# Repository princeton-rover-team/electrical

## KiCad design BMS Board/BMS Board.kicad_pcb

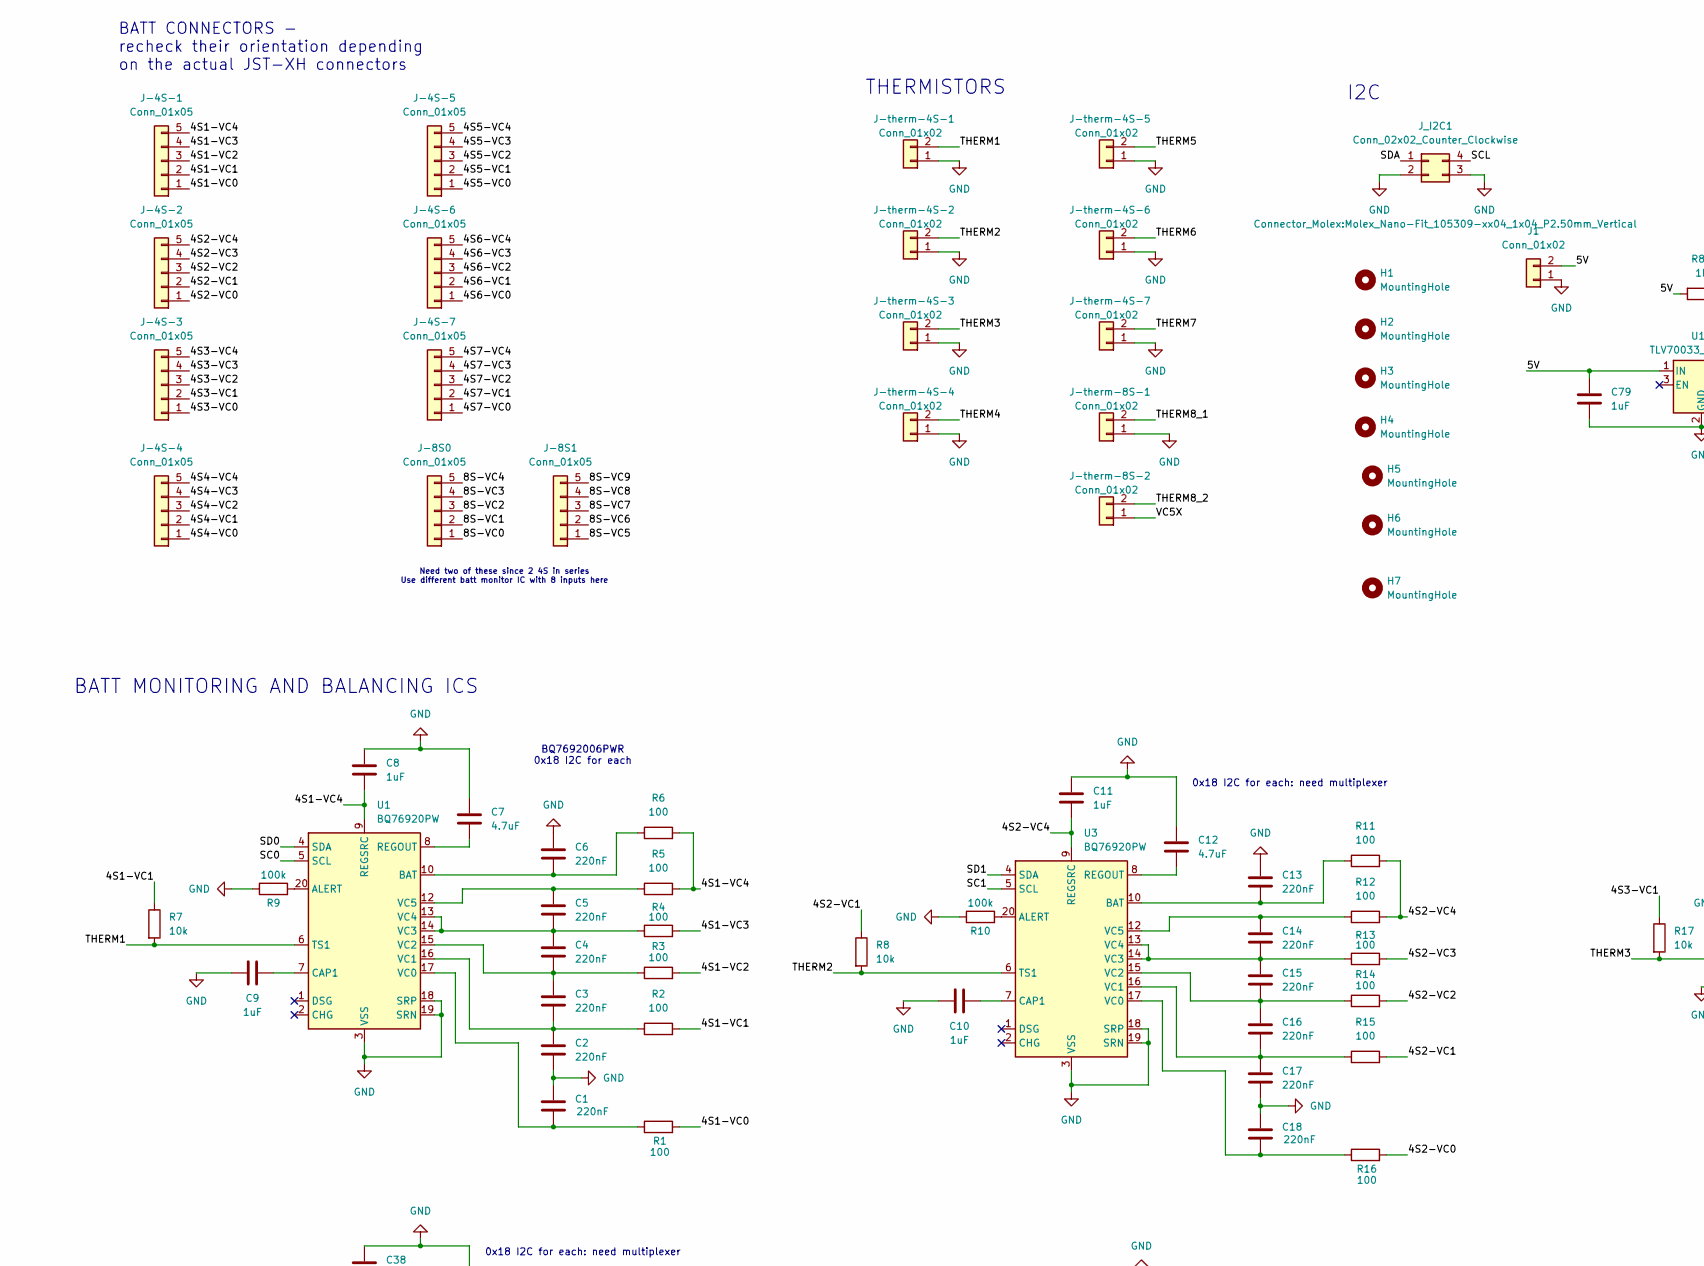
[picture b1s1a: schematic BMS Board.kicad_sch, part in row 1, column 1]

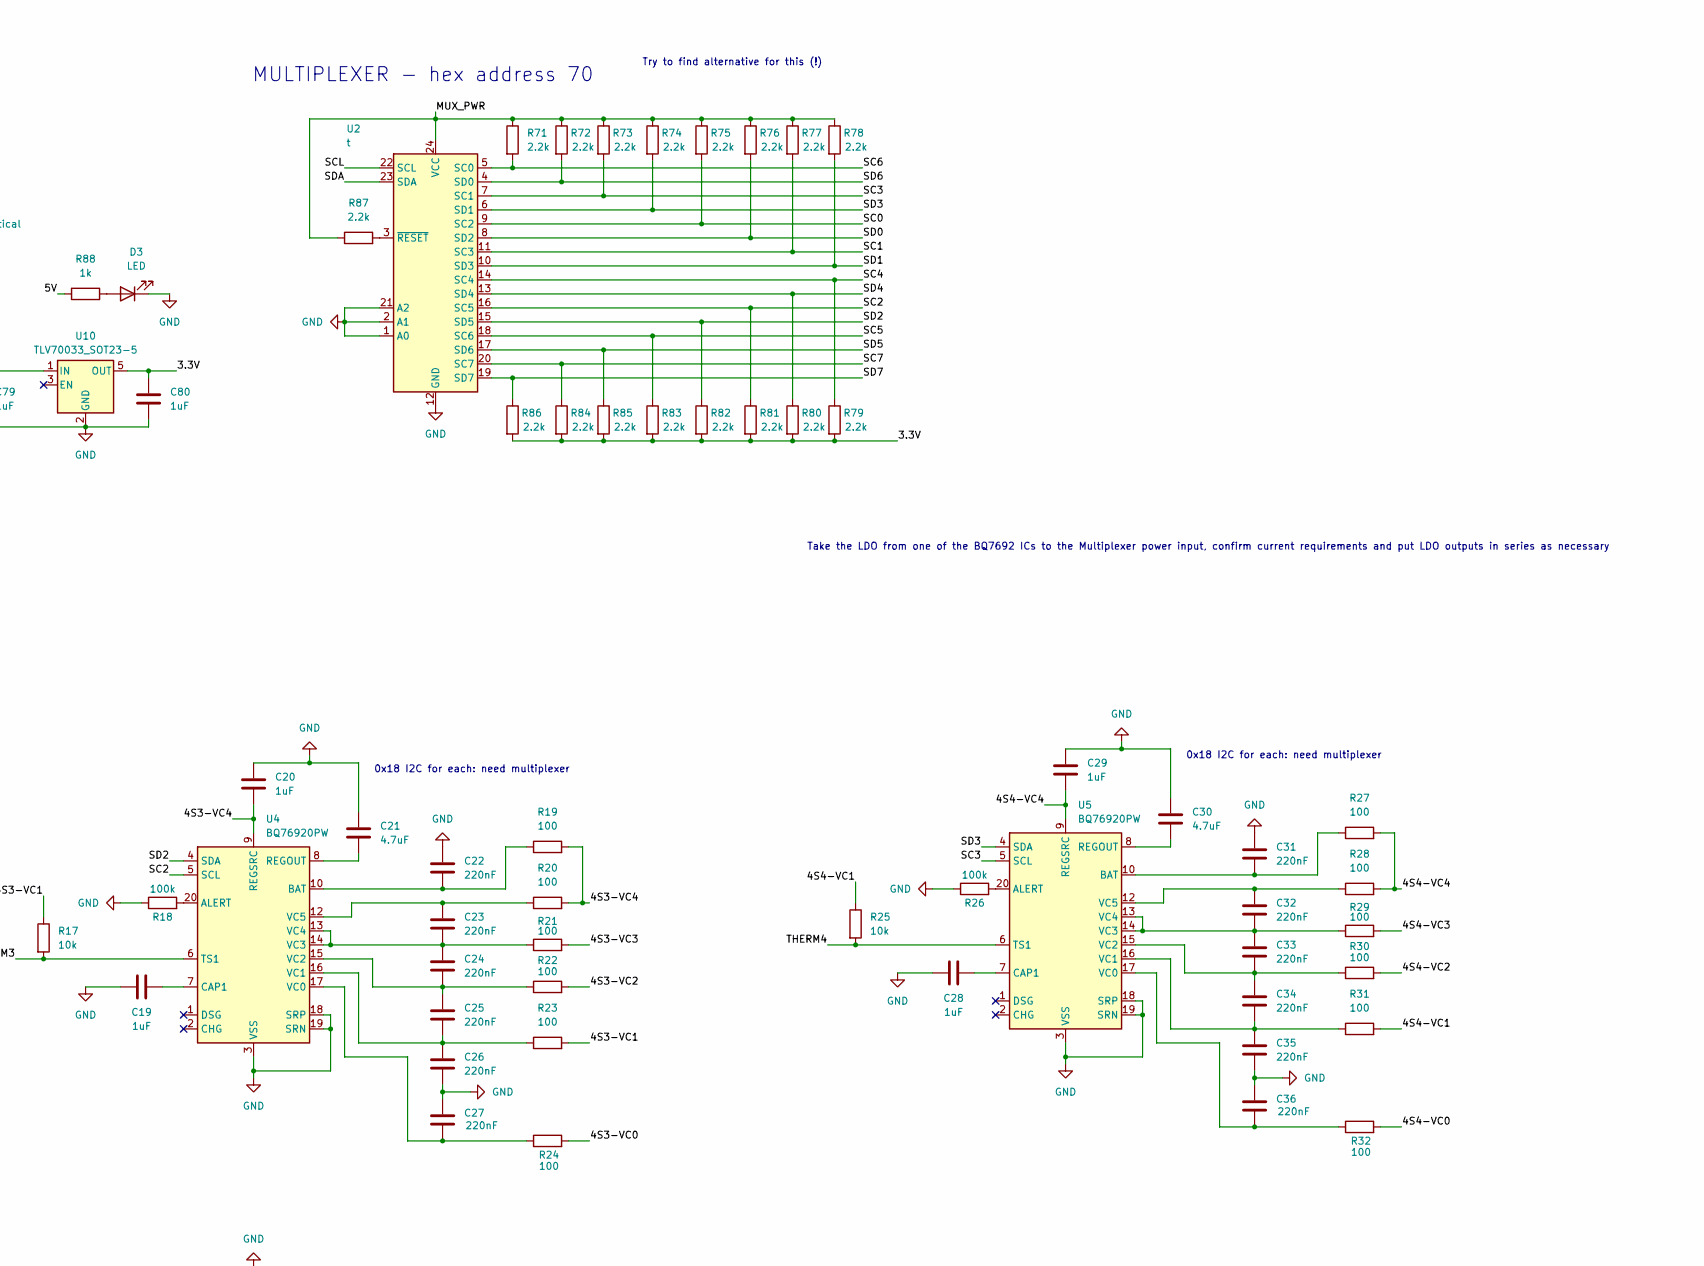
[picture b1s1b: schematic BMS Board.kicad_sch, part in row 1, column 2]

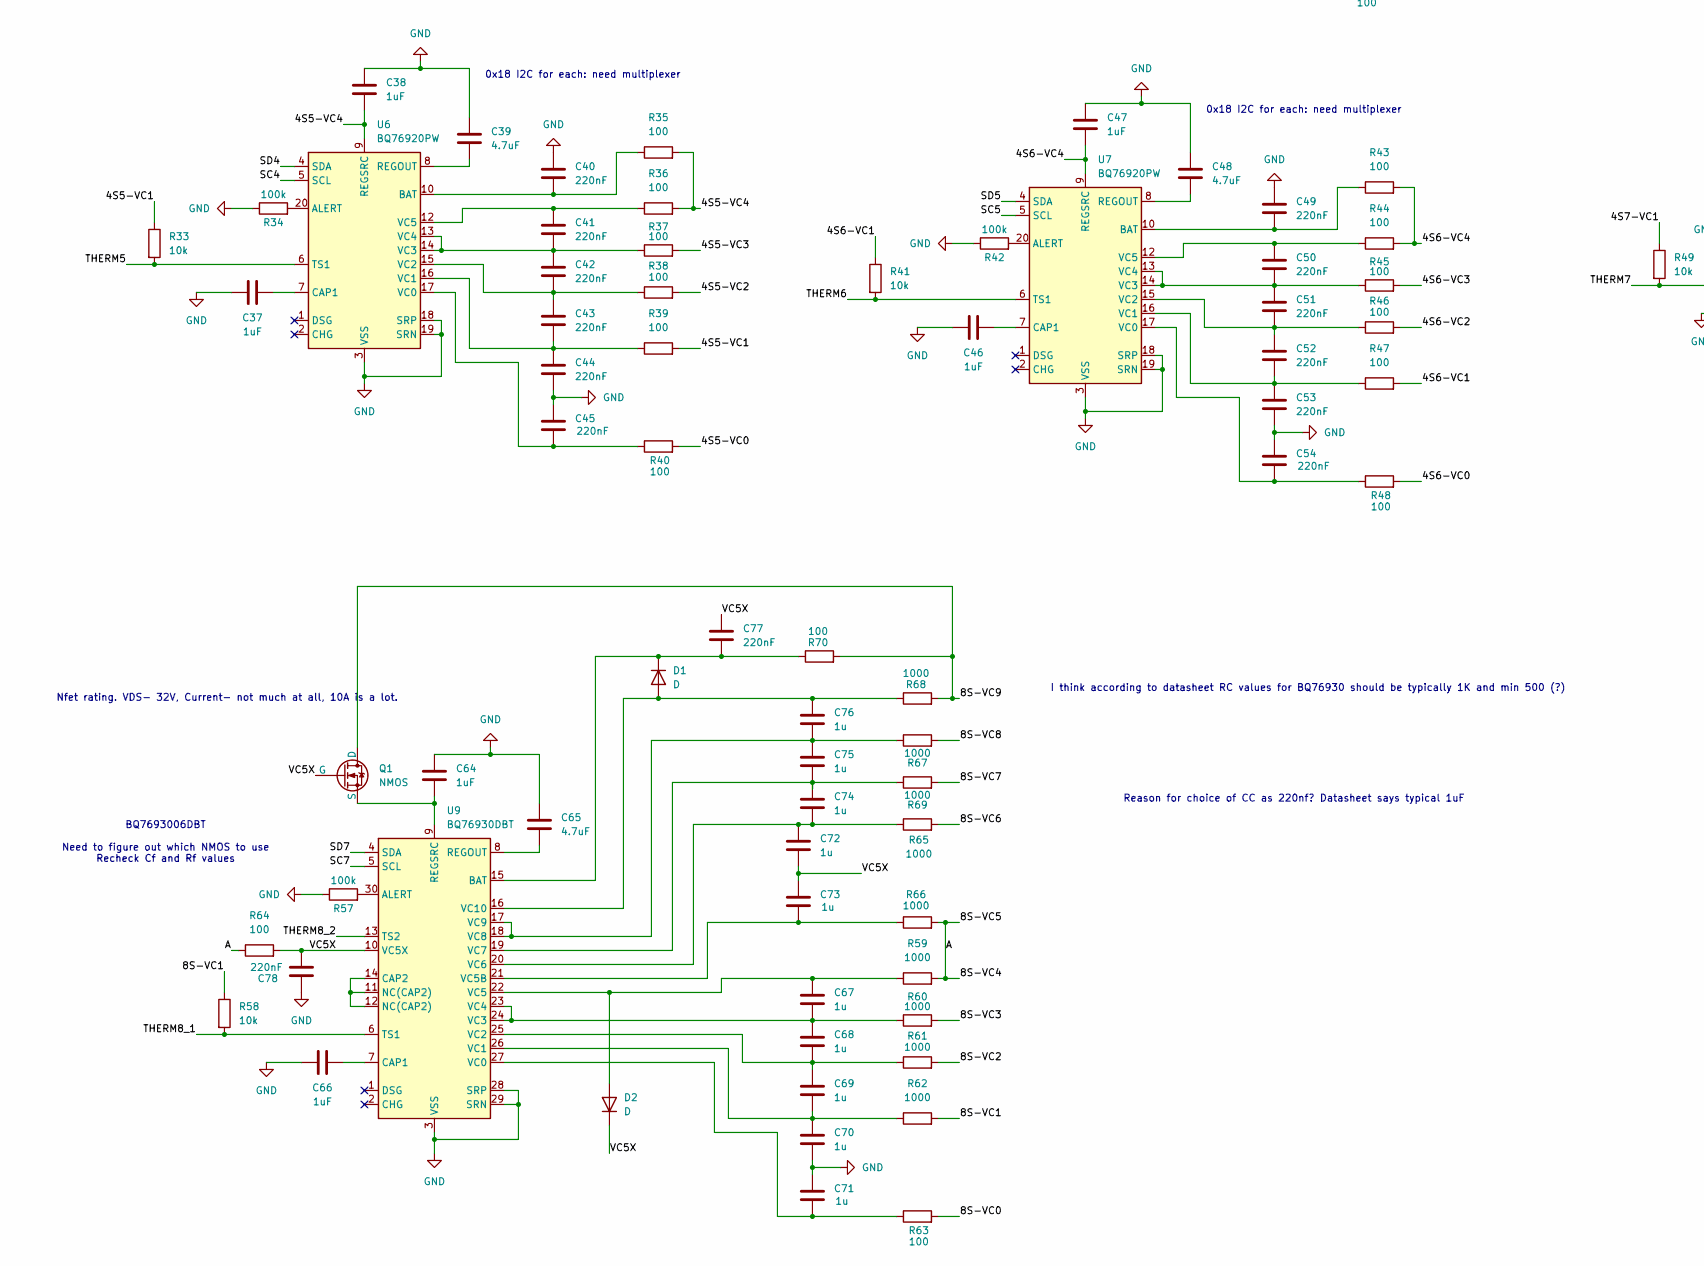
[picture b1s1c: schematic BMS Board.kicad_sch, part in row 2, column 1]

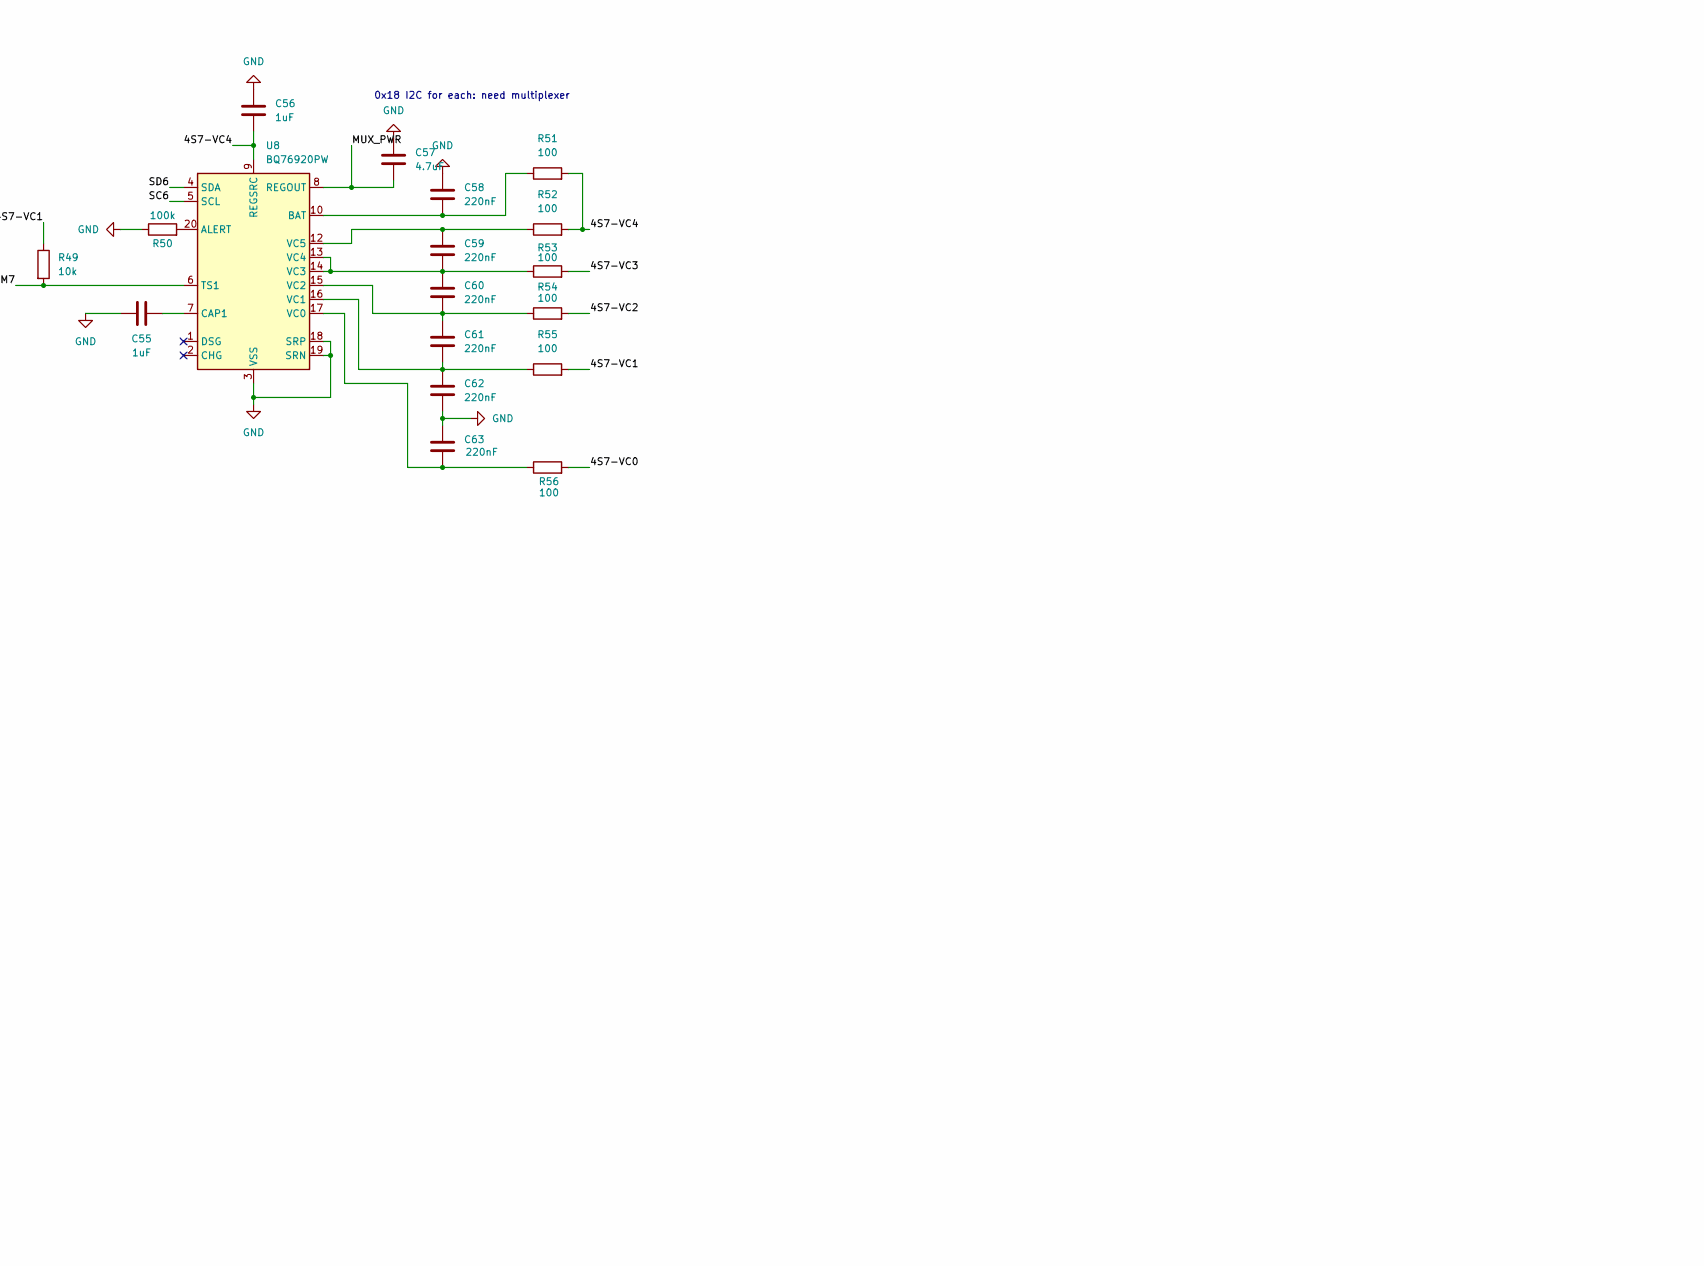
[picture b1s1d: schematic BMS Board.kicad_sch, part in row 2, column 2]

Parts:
C1, C2, C3, C4, C5, C6, C13, C14, C15, C16, C17, C18, C22, C23, C24, C25, C26, C27, C31, C32, C33, C34, C35, C36, C40, C41, C42, C43, C44, C45, C49, C50, C51, C52, C53, C54, C58, C59, C60, C61, C62, C63, C77, C78: 220nF; C_0603_1608Metric
C7, C12, C21, C30, C39, C48, C57, C65: 4.7uF; C_0603_1608Metric
C8, C9, C10, C11, C19, C20, C28, C29, C37, C38, C46, C47, C55, C56, C64, C66, C79, C80: 1uF; C_0603_1608Metric
C67, C68, C69, C70, C71, C72, C73, C74, C75, C76: 1u; C_0603_1608Metric
D1, D2: D; D_SOD-123
D3: LED; D_0603_1608Metric
H1, H2, H3, H4, H5, H6, H7: MountingHole; MountingHole_3.2mm_M3_DIN965
J1: Conn_01x02; AMASS_XT30UPB-F_1x02_P5.0mm_Vertical
J-4S-1, J-4S-2, J-4S-3, J-4S-4, J-4S-5, J-4S-6, J-4S-7, J-8S0, J-8S1: Conn_01x05; JST_XH_B5B-XH-A_1x05_P2.50mm_Vertical
J-therm-4S-1, J-therm-4S-2, J-therm-4S-3, J-therm-4S-4, J-therm-4S-5, J-therm-4S-6, J-therm-4S-7, J-therm-8S-1, J-therm-8S-2: Conn_01x02; Molex_KK-254_AE-6410-02A_1x02_P2.54mm_Vertical; MANUFACTURER_PART_NUMBER 768290102
J_I2C1: Conn_02x02_Counter_Clockwise; Molex_Nano-Fit_105309-xx04_1x04_P2.50mm_Vertical
Q1: NMOS; SOT-23
R1, R2, R3, R4, R5, R6, R11, R12, R13, R14, R15, R16, R19, R20, R21, R22, R23, R24, R27, R28, R29, R30, R31, R32, R35, R36, R37, R38, R39, R40, R43, R44, R45, R46, R47, R48, R51, R52, R53, R54, R55, R56, R63, R64, R70: 100; C_0603_1608Metric
R7, R8, R17, R25, R33, R41, R49, R58: 10k; C_0603_1608Metric
R9, R10, R18, R26, R34, R42, R50, R57: 100k; C_0603_1608Metric
R59, R60, R61, R62, R65, R66, R67, R68, R69: 1000; C_0603_1608Metric
R71, R72, R73, R74, R75, R76, R77, R78, R79, R80, R81, R82, R83, R84, R85, R86, R87: 2.2k; C_0603_1608Metric
R88: 1k; R_0805_2012Metric
U1, U3, U4, U5, U6, U7, U8: BQ76920PW; TSSOP-20_4.4x6.5mm_P0.65mm
U2: t; TSSOP-24_4.4x7.8mm_P0.65mm
U9: BQ76930DBT; TSSOP-30_4.4x7.8mm_P0.5mm
U10: TLV70033_SOT23-5; SOT-23-5

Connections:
/3.3V: C80.1, R79.2, R80.2, R81.2, R82.2, R83.2, R84.2, R85.2, R86.2, U10.5 (OUT)
/4S1-VC0: J-4S-1.1, R1.2
/4S1-VC1: J-4S-1.2, R2.2, R7.1
/4S1-VC2: J-4S-1.3, R3.2
/4S1-VC3: J-4S-1.4, R4.2
/4S1-VC4: C8.2, J-4S-1.5, R5.2, R6.2, U1.9 (REGSRC)
/4S2-VC0: J-4S-2.1, R16.2
/4S2-VC1: J-4S-2.2, R8.1, R15.2
/4S2-VC2: J-4S-2.3, R14.2
/4S2-VC3: J-4S-2.4, R13.2
/4S2-VC4: C11.2, J-4S-2.5, R11.2, R12.2, U3.9 (REGSRC)
/4S3-VC0: J-4S-3.1, R24.2
/4S3-VC1: J-4S-3.2, R17.1, R23.2
/4S3-VC2: J-4S-3.3, R22.2
/4S3-VC3: J-4S-3.4, R21.2
/4S3-VC4: C20.2, J-4S-3.5, R19.2, R20.2, U4.9 (REGSRC)
/4S4-VC0: J-4S-4.1, R32.2
/4S4-VC1: J-4S-4.2, R25.1, R31.2
/4S4-VC2: J-4S-4.3, R30.2
/4S4-VC3: J-4S-4.4, R29.2
/4S4-VC4: C29.2, J-4S-4.5, R27.2, R28.2, U5.9 (REGSRC)
/4S5-VC0: J-4S-5.1, R40.2
/4S5-VC1: J-4S-5.2, R33.1, R39.2
/4S5-VC2: J-4S-5.3, R38.2
/4S5-VC3: J-4S-5.4, R37.2
/4S5-VC4: C38.2, J-4S-5.5, R35.2, R36.2, U6.9 (REGSRC)
/4S6-VC0: J-4S-6.1, R48.2
/4S6-VC1: J-4S-6.2, R41.1, R47.2
/4S6-VC2: J-4S-6.3, R46.2
/4S6-VC3: J-4S-6.4, R45.2
/4S6-VC4: C47.2, J-4S-6.5, R43.2, R44.2, U7.9 (REGSRC)
/4S7-VC0: J-4S-7.1, R56.2
/4S7-VC1: J-4S-7.2, R49.1, R55.2
/4S7-VC2: J-4S-7.3, R54.2
/4S7-VC3: J-4S-7.4, R53.2
/4S7-VC4: C56.2, J-4S-7.5, R51.2, R52.2, U8.9 (REGSRC)
/5V: C79.1, J1.2, R88.2, U10.1 (IN)
/8S-VC0: J-8S0.1, R63.2
/8S-VC1: J-8S0.2, R58.1, R62.2
/8S-VC2: J-8S0.3, R61.2
/8S-VC3: J-8S0.4, R60.2
/8S-VC4: J-8S0.5, J-8S1.1, R59.2, R64.1, R66.2
/8S-VC6: J-8S1.2, R65.2
/8S-VC7: J-8S1.3, R69.2
/8S-VC8: J-8S1.4, R67.2
/8S-VC9: J-8S1.5, Q1.1 (D), R68.2, R70.2
/MUX_PWR: C57.2, R71.1, R72.1, R73.1, R74.1, R75.1, R76.1, R77.1, R78.1, R87.1, U2.24 (VCC), U8.8 (REGOUT)
/SC0: R75.2, U1.5 (SCL), U2.9 (SC2)
/SC1: R77.2, U2.11 (SC3), U3.5 (SCL)
/SC2: R81.1, U2.16 (SC5), U4.5 (SCL)
/SC3: R73.2, U2.7 (SC1), U5.5 (SCL)
/SC4: R79.1, U2.14 (SC4), U6.5 (SCL)
/SC5: R83.1, U2.18 (SC6), U7.5 (SCL)
/SC6: R71.2, U2.5 (SC0), U8.5 (SCL)
/SC7: R84.1, U2.20 (SC7), U9.5 (SCL)
/SCL: J_I2C1.4, U2.22 (SCL)
/SD0: R76.2, U1.4 (SDA), U2.8 (SD2)
/SD1: R78.2, U2.10 (SD3), U3.4 (SDA)
/SD2: R82.1, U2.15 (SD5), U4.4 (SDA)
/SD3: R74.2, U2.6 (SD1), U5.4 (SDA)
/SD4: R80.1, U2.13 (SD4), U6.4 (SDA)
/SD5: R85.1, U2.17 (SD6), U7.4 (SDA)
/SD6: R72.2, U2.4 (SD0), U8.4 (SDA)
/SD7: R86.1, U2.19 (SD7), U9.4 (SDA)
/SDA: J_I2C1.1, U2.23 (SDA)
/THERM1: J-therm-4S-1.2, R7.2, U1.6 (TS1)
/THERM2: J-therm-4S-2.2, R8.2, U3.6 (TS1)
/THERM3: J-therm-4S-3.2, R17.2, U4.6 (TS1)
/THERM4: J-therm-4S-4.2, R25.2, U5.6 (TS1)
/THERM5: J-therm-4S-5.2, R33.2, U6.6 (TS1)
/THERM6: J-therm-4S-6.2, R41.2, U7.6 (TS1)
/THERM7: J-therm-4S-7.2, R49.2, U8.6 (TS1)
/THERM8_1: J-therm-8S-1.2, R58.2, U9.6 (TS1)
/THERM8_2: J-therm-8S-2.2, U9.13 (TS2)
/VC5X: C72.2, C73.1, C77.1, C78.2, D2.1 (K), J-therm-8S-2.1, Q1.2 (G), R64.2, U9.10 (VC5X)
GND: C1.1, C2.2, C6.1, C7.1, C8.1, C9.2, C10.2, C11.1, C12.1, C13.1, C17.2, C18.1, C19.2, C20.1, C21.1, C22.1, C26.2, C27.1, C28.2, C29.1, C30.1, C31.1, C35.2, C36.1, C37.2, C38.1, C39.1, C40.1, C44.2, C45.1, C46.2, C47.1, C48.1, C49.1, C53.2, C54.1, C55.2, C56.1, C57.1, C58.1, C62.2, C63.1, C64.1, C65.1, C66.2, C70.2, C71.1, C78.1, C79.2, C80.2, D3.1 (K), J1.1, J-therm-4S-1.1, J-therm-4S-2.1, J-therm-4S-3.1, J-therm-4S-4.1, J-therm-4S-5.1, J-therm-4S-6.1, J-therm-4S-7.1, J-therm-8S-1.1, J_I2C1.2, J_I2C1.3, R9.1, R10.1, R18.1, R26.1, R34.1, R42.1, R50.1, R57.1, U1.3 (VSS), U1.18 (SRP), U1.19 (SRN), U2.1 (A0), U2.2 (A1), U2.12 (GND), U2.21 (A2), U3.3 (VSS), U3.18 (SRP), U3.19 (SRN), U4.3 (VSS), U4.18 (SRP), U4.19 (SRN), U5.3 (VSS), U5.18 (SRP), U5.19 (SRN), U6.3 (VSS), U6.18 (SRP), U6.19 (SRN), U7.3 (VSS), U7.18 (SRP), U7.19 (SRN), U8.3 (VSS), U8.18 (SRP), U8.19 (SRN), U9.3 (VSS), U9.28 (SRP), U9.29 (SRN), U10.2 (GND)
unnamed: C76.1, D1.2 (A), R68.1, U9.16 (VC10)
unnamed: C77.2, D1.1 (K), R70.1, U9.15 (BAT)
unnamed: C67.1, D2.2 (A), R59.1, U9.22 (VC5)
unnamed: D3.2 (A), R88.1
unnamed: C64.2, Q1.3 (S), U9.9 (REGSRC)
unnamed: R9.2, U1.20 (ALERT)
unnamed: C6.2, R6.1, U1.10 (BAT)
unnamed: C9.1, U1.7 (CAP1)
unnamed: C7.2, U1.8 (REGOUT)
unnamed: C1.2, R1.1, U1.17 (VC0)
unnamed: C2.1, C3.2, R2.1, U1.16 (VC1)
unnamed: C3.1, C4.2, R3.1, U1.15 (VC2)
unnamed: C4.1, C5.2, R4.1, U1.13 (VC4), U1.14 (VC3)
unnamed: C5.1, R5.1, U1.12 (VC5)
unnamed: R87.2, U2.3 (~RESET)
unnamed: R10.2, U3.20 (ALERT)
unnamed: C13.2, R11.1, U3.10 (BAT)
unnamed: C10.1, U3.7 (CAP1)
unnamed: C12.2, U3.8 (REGOUT)
unnamed: C18.2, R16.1, U3.17 (VC0)
unnamed: C16.2, C17.1, R15.1, U3.16 (VC1)
unnamed: C15.2, C16.1, R14.1, U3.15 (VC2)
unnamed: C14.2, C15.1, R13.1, U3.13 (VC4), U3.14 (VC3)
unnamed: C14.1, R12.1, U3.12 (VC5)
unnamed: R18.2, U4.20 (ALERT)
unnamed: C22.2, R19.1, U4.10 (BAT)
unnamed: C19.1, U4.7 (CAP1)
unnamed: C21.2, U4.8 (REGOUT)
unnamed: C27.2, R24.1, U4.17 (VC0)
unnamed: C25.2, C26.1, R23.1, U4.16 (VC1)
unnamed: C24.2, C25.1, R22.1, U4.15 (VC2)
unnamed: C23.2, C24.1, R21.1, U4.13 (VC4), U4.14 (VC3)
unnamed: C23.1, R20.1, U4.12 (VC5)
unnamed: R26.2, U5.20 (ALERT)
unnamed: C31.2, R27.1, U5.10 (BAT)
unnamed: C28.1, U5.7 (CAP1)
unnamed: C30.2, U5.8 (REGOUT)
unnamed: C36.2, R32.1, U5.17 (VC0)
unnamed: C34.2, C35.1, R31.1, U5.16 (VC1)
unnamed: C33.2, C34.1, R30.1, U5.15 (VC2)
unnamed: C32.2, C33.1, R29.1, U5.13 (VC4), U5.14 (VC3)
unnamed: C32.1, R28.1, U5.12 (VC5)
unnamed: R34.2, U6.20 (ALERT)
unnamed: C40.2, R35.1, U6.10 (BAT)
unnamed: C37.1, U6.7 (CAP1)
unnamed: C39.2, U6.8 (REGOUT)
unnamed: C45.2, R40.1, U6.17 (VC0)
unnamed: C43.2, C44.1, R39.1, U6.16 (VC1)
unnamed: C42.2, C43.1, R38.1, U6.15 (VC2)
unnamed: C41.2, C42.1, R37.1, U6.13 (VC4), U6.14 (VC3)
unnamed: C41.1, R36.1, U6.12 (VC5)
unnamed: R42.2, U7.20 (ALERT)
unnamed: C49.2, R43.1, U7.10 (BAT)
unnamed: C46.1, U7.7 (CAP1)
unnamed: C48.2, U7.8 (REGOUT)
unnamed: C54.2, R48.1, U7.17 (VC0)
unnamed: C52.2, C53.1, R47.1, U7.16 (VC1)
unnamed: C51.2, C52.1, R46.1, U7.15 (VC2)
unnamed: C50.2, C51.1, R45.1, U7.13 (VC4), U7.14 (VC3)
unnamed: C50.1, R44.1, U7.12 (VC5)
unnamed: R50.2, U8.20 (ALERT)
unnamed: C58.2, R51.1, U8.10 (BAT)
unnamed: C55.1, U8.7 (CAP1)
unnamed: C63.2, R56.1, U8.17 (VC0)
unnamed: C61.2, C62.1, R55.1, U8.16 (VC1)
unnamed: C60.2, C61.1, R54.1, U8.15 (VC2)
unnamed: C59.2, C60.1, R53.1, U8.13 (VC4), U8.14 (VC3)
unnamed: C59.1, R52.1, U8.12 (VC5)
unnamed: R57.2, U9.30 (ALERT)
unnamed: C66.1, U9.7 (CAP1)
unnamed: U9.11 (NC(CAP2)), U9.12 (NC(CAP2)), U9.14 (CAP2)
unnamed: C65.2, U9.8 (REGOUT)
unnamed: C71.2, R63.1, U9.27 (VC0)
unnamed: C69.2, C70.1, R62.1, U9.26 (VC1)
unnamed: C68.2, C69.1, R61.1, U9.25 (VC2)
unnamed: C67.2, C68.1, R60.1, U9.23 (VC4), U9.24 (VC3)
unnamed: C73.2, R66.1, U9.21 (VC5B)
unnamed: C72.1, C74.2, R65.1, U9.20 (VC6)
unnamed: C74.1, C75.2, R69.1, U9.19 (VC7)
unnamed: C75.1, C76.2, R67.1, U9.17 (VC9), U9.18 (VC8)

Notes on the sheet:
Reason for choice of CC as 220nf? Datasheet says typical 1uF
0x18 I2C for each: need multiplexer
Need two of these since 2 4S in series Use different batt monitor IC with 8 inputs here
I2C
BATT MONITORING AND BALANCING ICS
Take the LDO from one of the BQ7692 ICs to the Multiplexer power input, confirm current requirements and put LDO outputs in series as necessary
THERMISTORS
BATT CONNECTORS - recheck their orientation depending on the actual JST-XH connectors
I think according to datasheet RC values for BQ76930 should be typically 1K and min 500 (?)
BQ7692006PWR 0x18 I2C for each
MULTIPLEXER - hex address 70
Try to find alternative for this (!)
Nfet rating. VDS- 32V, Current- not much at all, 10A is a lot.
BQ7693006DBT Need to figure out which NMOS to use Recheck Cf and Rf values

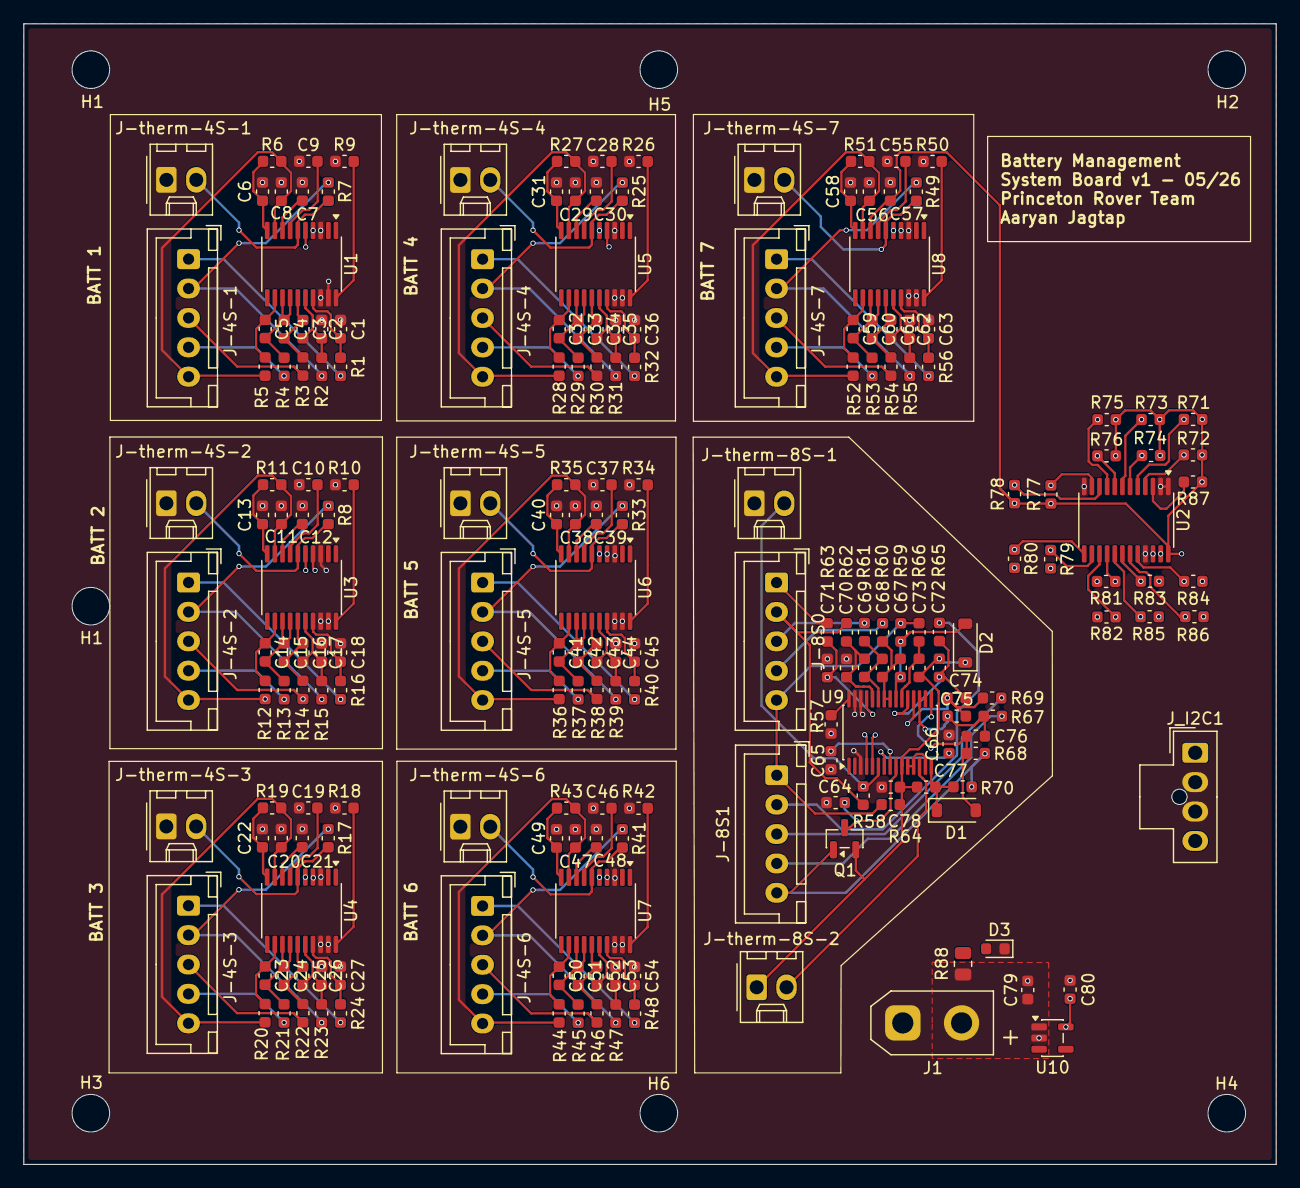
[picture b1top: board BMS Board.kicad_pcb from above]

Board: 4 copper layers, 106.5 x 97.0 mm, 209 parts (0 on the bottom side), 156 nets.

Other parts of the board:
H1#2: MountingHole; MountingHole_3.2mm_M3_DIN965
